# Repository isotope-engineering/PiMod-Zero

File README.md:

# PiMod Zero

The PiMod Zero brings old tech back to life by allowing a Raspberry Pi Zero to display color or B&W video—and play audio—on vintage televisions. It provides a super-compact way to watch old movies, play retro games, present digital art, or navigate your operating system using any television that receives standard NTSC broadcasts on VHF channels 2 and 3 (55.25 MHz and 61.25 MHz).

In the past, you would have needed a cumbersome RF modulator box to adapt the HDMI signal from a Pi Zero. Now, with this convenient HAT snapped on top of your Pi Zero, no additional dongles are required. In fact, once the Pi is powered up, the only other cable you need is a piece of coax to connect the PiMod Zero to your TV.

## Features
- Supports color and B&W video
- Supports audio
- Small form factor
- No external power supply
- Low power
- Open Source

## Tech Specs
- Operating frequency: VHF channels 2 and 3 (55.25 MHz and 61.25 MHz)
- Broadcast format: NTSC
- Supply voltage: 5V
- RF output power: 0.005 mW
- Impedance: 75 Ω
- Power draw: 100 mW 

## Getting Started
Check out the [Setup directory](/setup).

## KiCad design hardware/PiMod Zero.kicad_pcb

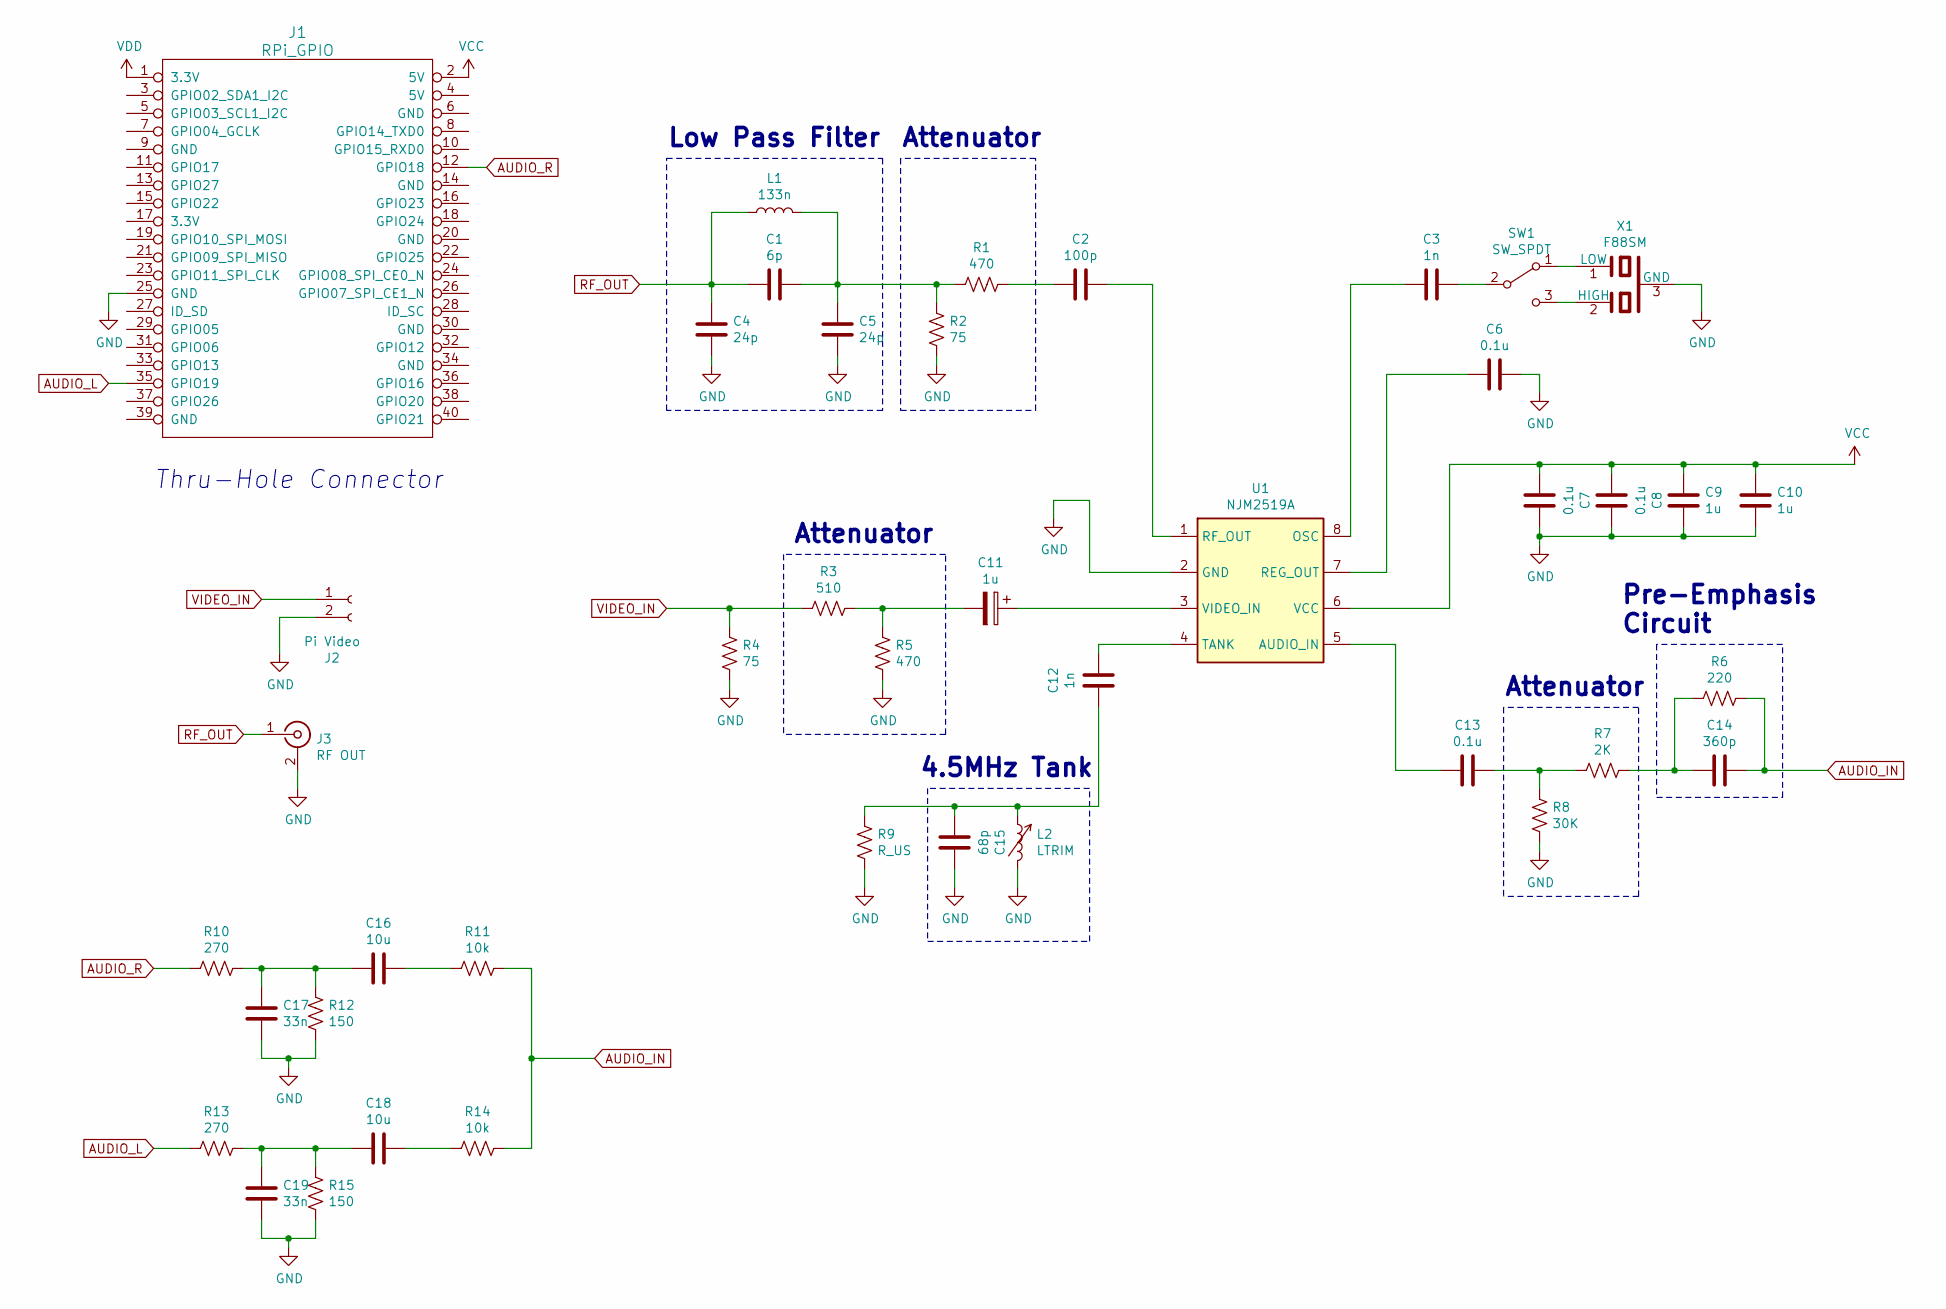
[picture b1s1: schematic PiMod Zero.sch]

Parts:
C1: 6p; C_0805_2012Metric; Voltage 50V; Tolerance 10%
C2: 100p; C_0805_2012Metric; Voltage 50V; Tolerance 10%
C3: 1n; C_0805_2012Metric; Voltage 50V; Tolerance 10%
C4, C5: 24p; C_0805_2012Metric; Voltage 50V; Tolerance 10%
C6, C7, C8, C13: 0.1u; C_0805_2012Metric; Voltage 50V; Tolerance 10%
C9, C10: 1u; C_0805_2012Metric; Voltage 50V; Tolerance 10%
C11: 1u; C_1206_3216Metric; Voltage 50V; Tolerance 10%
C12: 1n; C_0805_2012Metric; Voltage 50; Tolerance 10%
C14: 360p; C_0805_2012Metric; Voltage 50V; Tolerance 10%
C15: 68p; C_0805_2012Metric; Voltage 50V; Tolerance 1%
C16, C18: 10u; C_0805_2012Metric; Voltage 50V; Tolerance 10%
C17, C19: 33n; C_0805_2012Metric; Voltage 50V; Tolerance 10%
J1: RPi_GPIO; PinHeader_2x20_P2.54mm_Vertical; Part Number Adafruit 2222
J2: Pi Video; PinHeader_1x02_P2.54mm_Vertical; Part Number 90147-1102
J3: RF OUT; 531400473; Part Number 73330-0030
L1: 133n; Wurth_WE_Inductor_744918213; Tolerance 5%; Part Number 744918213
L2: LTRIM; Coilcraft Slot 7 Inductor; Part Number Coilcraft 7M3-183
R1, R5: 470; R_0805_2012Metric; Tolerance 5%
R2, R4: 75; R_0805_2012Metric; Tolerance 0.5%
R3: 510; R_0805_2012Metric; Tolerance 5%
R6: 220; R_0805_2012Metric; Tolerance 5%
R7: 2K; R_0805_2012Metric; Tolerance 5%
R8: 30K; R_0805_2012Metric; Tolerance 5%
R9: R_US; R_0805_2012Metric
R10, R13: 270; R_0805_2012Metric; Tolerance 5%
R11, R14: 10k; R_0805_2012Metric; Tolerance 5%
R12, R15: 150; R_0805_2012Metric; Tolerance 5%
SW1: SW_SPDT; SW_SPDT_PCM12; Part Number MSS3-V-T/R
U1: NJM2519A; SOIC-8_5.23x5.23mm_P1.27mm; Part Number NJM2519A
X1: F88SM; Part Number F88SM

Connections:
AUDIO_IN: C14.1, R6.1, R11.1, R14.1
AUDIO_L: J1.35 (GPIO19), R13.2
AUDIO_R: J1.12 (GPIO18), R10.2
unnamed: C1.1, C5.1, L1.2, R1.2, R2.1
unnamed: C2.1, U1.1 (RF_OUT)
unnamed: C2.2, R1.1
unnamed: C3.1, SW1.2 (B)
unnamed: C3.2, U1.8 (OSC)
unnamed: C6.2, U1.7 (REG_OUT)
unnamed: C11.1, U1.3 (VIDEO_IN)
unnamed: C11.2, R3.1, R5.1
unnamed: C12.1, U1.4 (TANK)
unnamed: C12.2, C15.2, L2.1, R9.1
unnamed: C13.1, R7.2, R8.1
unnamed: C13.2, U1.5 (AUDIO_IN)
unnamed: C14.2, R6.2, R7.1
unnamed: C16.1, R11.2
unnamed: C16.2, C17.1, R10.1, R12.1
unnamed: C18.1, R14.2
unnamed: C18.2, C19.1, R13.1, R15.1
unnamed: SW1.1 (A), X1.1 (LOW)
unnamed: SW1.3 (C), X1.2 (HIGH)
VCC: C7.2, C8.2, C9.2, C10.2, J1.2 (5V), U1.6 (VCC)
VDD: J1.1 (3.3V)
VIDEO_IN: J2.1, R3.2, R4.1

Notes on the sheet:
Low Pass Filter
Attenuator
Pre-Emphasis Circuit
4.5MHz Tank
Thru-Hole Connector

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
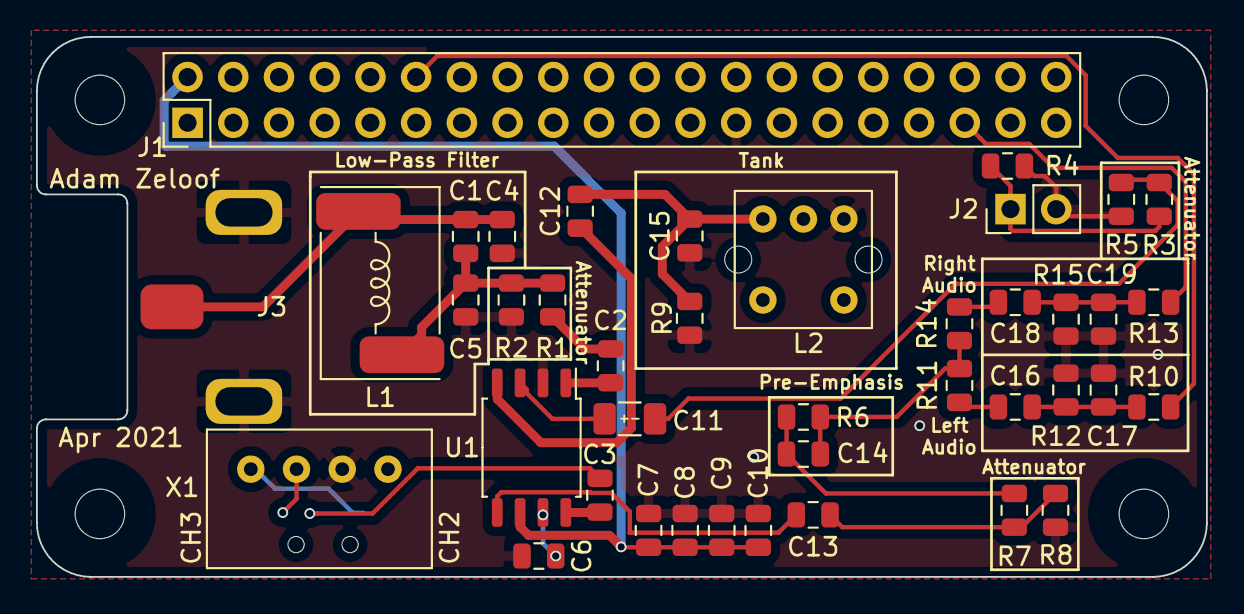
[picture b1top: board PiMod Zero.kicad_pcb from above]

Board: 2 copper layers, 65.0 x 30.0 mm, 42 parts (1 on the bottom side), 26 nets.

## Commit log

2020-08-02 Initial Commit
    Migrated from old repo
2020-08-07 Added PLL to schematic
2020-08-08 Connected Clocks in Schematic
2021-04-04 Changed board profile and F connector
2021-04-13 Documentation Update
2021-04-13 Cleanup
2021-04-14 Updated 3D models
2021-04-15 Added BOM
2021-04-27 Added 3D Printed Case
2021-07-28 Updated setup instructions
2021-07-28 Setup instructions formatting
2021-07-29 Wrote audio setup script (untested)
